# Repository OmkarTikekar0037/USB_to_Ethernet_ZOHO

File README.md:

# USB 3.1 Gen 1 to Gigabit Ethernet Adapter

A custom 4-layer PCB implementing a USB 3.1 Gen 1 to Gigabit Ethernet adapter based on the **Microchip LAN7801** USB-to-Ethernet controller and the **KSZ9031RNX** Gigabit Ethernet PHY.

The project focuses on producing a manufacturable hardware design by following industry-standard practices for high-speed PCB layout, power distribution, signal integrity, and Ethernet design.

---

## Project Objectives

- Design a production-quality USB 3.1 Gen 1 to Gigabit Ethernet adapter.
- Implement a complete RGMII-based Ethernet subsystem.
- Develop a reliable multi-rail power architecture.
- Follow high-speed PCB design guidelines for USB and Gigabit Ethernet.
- Produce fabrication-ready design files with zero ERC/DRC violations.

---

## Hardware Overview

| Component | Description |
|-----------|-------------|
| LAN7801 | USB 3.1 Gen 1 to Gigabit Ethernet Controller |
| KSZ9031RNX | Gigabit Ethernet PHY |
| 93LC56 | External configuration EEPROM |
| USB Type-C | USB Interface |
| RJ45 MagJack | Ethernet Connector with Integrated Magnetics |
| TLV76733 | 3.3V LDO |
| TPS7A0212 | 1.2V LDO |

---

## System Architecture

```
USB Type-C
      │
      ▼
+--------------+
|   LAN7801    |
+--------------+
      │
     RGMII
      │
      ▼
+--------------+
| KSZ9031RNX   |
+--------------+
      │
 Ethernet MDI
      │
      ▼
 RJ45 MagJack
```

---

## Repository Structure

```text
.
├── Hardware/
│   ├── Schematic/
│   ├── PCB/
│   ├── Libraries/
│   └── Manufacturing/
│
├── Docs/
│   ├── Project_History.md
│   ├── System_Architecture.md
│   ├── Power_Architecture.md
│   ├── Ethernet_Subsystem.md
│   ├── USB_Subsystem.md
│   ├── PCB_Design.md
│   └── Debugging.md
│
├── Datasheets/
│
├── Images/
│
└── README.md
```

---

## Current Project Status

| Stage | Status |
|--------|--------|
| Component Selection | Completed |
| Schematic Design | Completed |
| PCB Placement | Completed |
| PCB Routing | Completed |
| ERC | Passed |
| DRC | Passed |
| Manufacturing Outputs | In Progress |
| Hardware Validation | Pending |

---

## Design Highlights

- 4-layer PCB stack-up
- Controlled impedance routing
- USB differential pair routing
- Gigabit Ethernet differential routing
- Dedicated power planes
- Multi-stage power regulation
- External EEPROM configuration
- RGMII interface between MAC and PHY
- ESD and signal protection provisions

---

## Documentation

Detailed design discussions and engineering decisions are maintained separately under the **Docs** directory.

These documents describe:

- Architecture
- Design decisions
- Power subsystem
- PCB layout methodology
- Signal integrity considerations
- Manufacturing preparation
- Debugging history

The README intentionally provides only a high-level overview.

---

## Future Work

- PCB fabrication
- Assembly
- Hardware bring-up
- USB enumeration verification
- Ethernet link validation
- Throughput testing
- Compliance verification

---

## License

Project license to be added.

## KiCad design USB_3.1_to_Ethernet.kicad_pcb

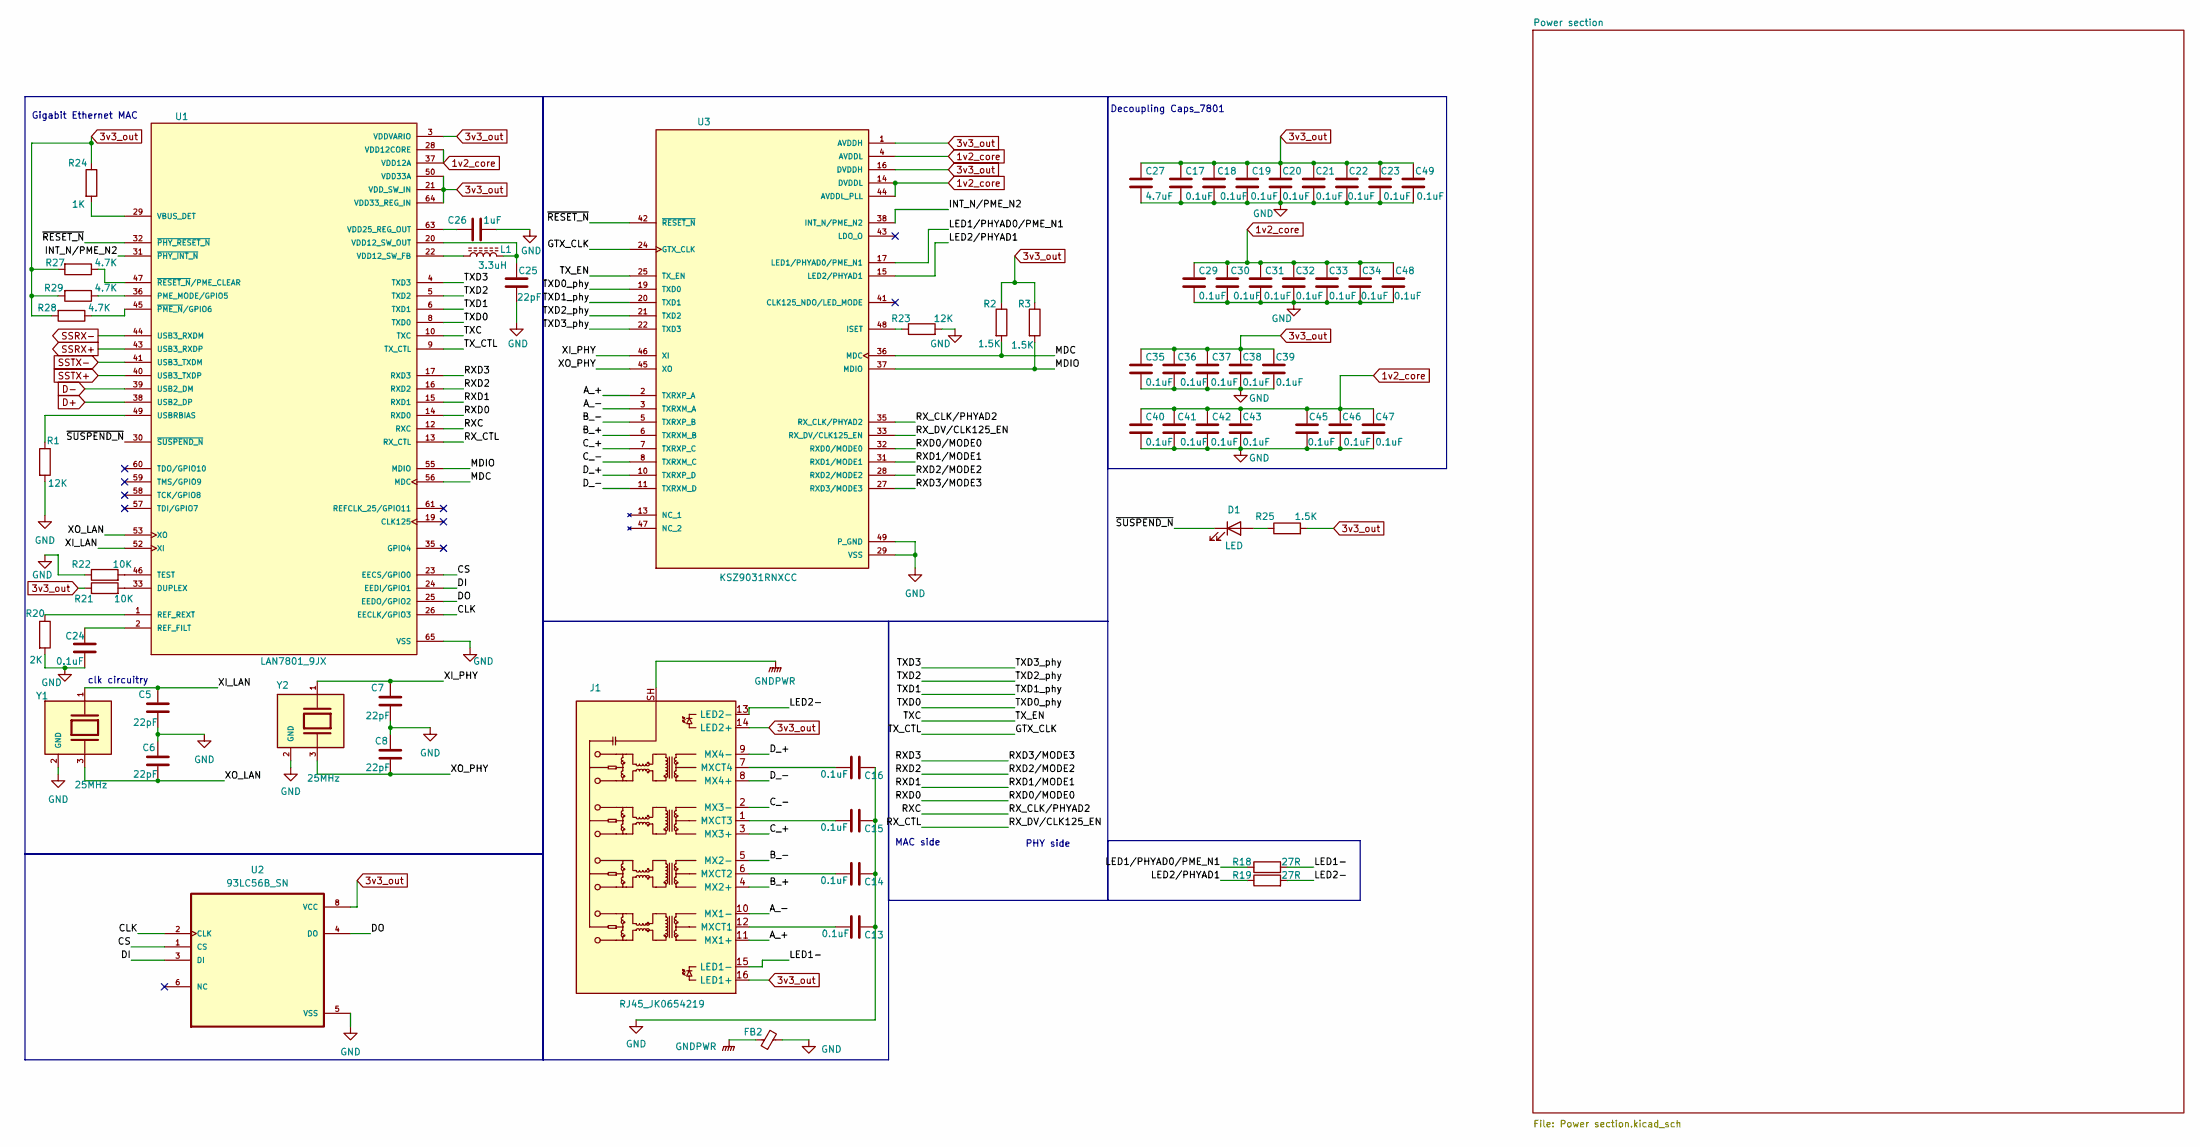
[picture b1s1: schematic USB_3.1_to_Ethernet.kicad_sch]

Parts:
C5, C6, C7, C8: 22pF; C_0402_1005Metric
C13, C14, C15, C16: 0.1uF; C_0402_1005Metric
C17, C18, C19, C20, C21, C22, C23, C24, C29, C30, C31, C32, C33, C34, C35, C36, C37, C38, C39, C40, C41, C42, C43, C45, C46, C47, C48, C49: 0.1uF; C_01005_0402Metric
C25: 22pF; C_01005_0402Metric
C26: 1uF; C_01005_0402Metric
C27: 4.7uF; C_01005_0402Metric
D1: LED; LED_01005_0402Metric
FB2: FerriteBead_Small; L_0402_1005Metric
J1: RJ45_JK0654219; RJ45_Pulse_JK0654219NL_Horizontal
L1: 3.3uH; L_0402_1005Metric
R1, R23: 12K; R_0402_1005Metric
R2, R3, R25: 1.5K; R_0402_1005Metric
R18, R19: 27R; R_0402_1005Metric
R20: 2K; R_0402_1005Metric
R21, R22: 10K; R_0402_1005Metric
R24: 1K; R_0402_1005Metric
R27, R28, R29: 4.7K; R_0402_1005Metric
U1: LAN7801_9JX; QFN50P900X900X100-65N_LAN7801_9JX; PARTREV DS00002123F
U2: 93LC56B_SN; 93LC56B_SOIC_8
U3: KSZ9031RNXCC; IC_KSZ9031RNXCC; PARTREV 07-09-24
Y1, Y2: 25MHz; Crystal_SMD_3225-4Pin_3.2x2.5mm; PARTREV August 01, 2022

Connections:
1v2_core: C29.1, C30.1, C31.1, C32.1, C33.1, C34.1, C40.1, C41.1, C42.1, C43.1, C45.1, C46.1, C47.1, C48.1, U1.28 (VDD12CORE), U1.37 (VDD12A), U1.42 (VDD12A), U1.54 (VDD12CORE), U1.62 (VDD12A), U3.4 (AVDDL), U3.9 (AVDDL), U3.14 (DVDDL), U3.18 (DVDDL), U3.23 (DVDDL), U3.26 (DVDDL), U3.30 (DVDDL), U3.39 (DVDDL), U3.44 (AVDDL_PLL); also elsewhere on the board
3v3_out: C17.1, C18.1, C19.1, C20.1, C21.1, C22.1, C23.1, C27.1, C35.1, C36.1, C37.1, C38.1, C39.1, C49.1, J1.14 (LED2+), J1.16 (LED1+), R2.1, R3.1, R21.1, R24.1, R25.2, R27.2, R28.2, R29.2, U1.3 (VDDVARIO), U1.7 (VDDVARIO), U1.11 (VDDVARIO), U1.18 (VDDVARIO), U1.21 (VDD_SW_IN), U1.27 (VDDVARIO), U1.48 (VDDVARIO), U1.50 (VDD33A), U1.51 (VDDVARIO), U1.64 (VDD33_REG_IN), U2.8 (VCC), U3.1 (AVDDH), U3.12 (AVDDH), U3.16 (DVDDH), U3.34 (DVDDH), U3.40 (DVDDH); also elsewhere on the board
/A_+: J1.11 (MX1+), U3.2 (TXRXP_A)
/A_-: J1.10 (MX1-), U3.3 (TXRXM_A)
/B_+: J1.4 (MX2+), U3.6 (TXRXM_B)
/B_-: J1.5 (MX2-), U3.5 (TXRXP_B)
/CLK: U1.26 (EECLK/GPIO3), U2.2 (CLK)
/CS: U1.23 (EECS/GPIO0), U2.1 (CS)
/C_+: J1.3 (MX3+), U3.7 (TXRXP_C)
/C_-: J1.2 (MX3-), U3.8 (TXRXM_C)
/DI: U1.24 (EEDI/GPIO1), U2.3 (DI)
/DO: U1.25 (EEDO/GPIO2), U2.4 (DO)
/D_+: J1.9 (MX4-), U3.10 (TXRXP_D)
/D_-: J1.8 (MX4+), U3.11 (TXRXM_D)
/GTX_CLK: U1.9 (TX_CTL), U3.24 (GTX_CLK)
/INT_N/PME_N2: U1.31 (~PHY_INT_N), U3.38 (INT_N/PME_N2)
/LED1-: J1.15 (LED1-), R18.2
/LED1/PHYAD0/PME_N1: R18.1, U3.17 (LED1/PHYAD0/PME_N1)
/LED2-: J1.13 (LED2-), R19.2
/LED2/PHYAD1: R19.1, U3.15 (LED2/PHYAD1)
/MDC: R2.2, U1.56 (MDC), U3.36 (MDC)
/MDIO: R3.2, U1.55 (MDIO), U3.37 (MDIO)
/RXD0: U1.14 (RXD0), U3.32 (RXD0/MODE0)
/RXD1: U1.15 (RXD1), U3.31 (RXD1/MODE1)
/RXD2: U1.16 (RXD2), U3.28 (RXD2/MODE2)
/RXD3: U1.17 (RXD3), U3.27 (RXD3/MODE3)
/RX_CTL: U1.13 (RX_CTL), U3.33 (RX_DV/CLK125_EN)
/TXC: U1.10 (TXC), U3.25 (TX_EN)
/TXD0: U1.8 (TXD0), U3.19 (TXD0)
/TXD1: U1.6 (TXD1), U3.20 (TXD1)
/TXD2: U1.5 (TXD2), U3.21 (TXD2)
/TXD3: U1.4 (TXD3), U3.22 (TXD3)
/XI_LAN: C5.1, U1.52 (XI), Y1.1
/XI_PHY: C7.1, U3.46 (XI), Y2.1
/XO_LAN: C6.2, U1.53 (XO), Y1.3
/XO_PHY: C8.2, U3.45 (XO), Y2.3
/~RESET_N: U1.32 (~PHY_RESET_N), U3.42 (~RESET_N)
/~SUSPEND_N: D1.1 (K), U1.30 (~SUSPEND_N)
D+: U1.38 (USB2_DP); also elsewhere on the board
D-: U1.39 (USB2_DM); also elsewhere on the board
GND: C5.2, C6.1, C7.2, C8.1, C13.1, C14.1, C15.1, C16.1, C17.2, C18.2, C19.2, C20.2, C21.2, C22.2, C23.2, C24.2, C25.2, C26.2, C27.2, C29.2, C30.2, C31.2, C32.2, C33.2, C34.2, C35.2, C36.2, C37.2, C38.2, C39.2, C40.2, C41.2, C42.2, C43.2, C45.2, C46.2, C47.2, C48.2, C49.2, FB2.2, R1.2, R20.2, R22.1, R23.2, U1.65 (VSS), U2.5 (VSS), U3.29 (VSS), U3.49 (P_GND), U3.49_1 (P_GND), U3.49_2 (P_GND), U3.49_3 (P_GND), U3.49_4 (P_GND), U3.49_5 (P_GND), U3.49_6 (P_GND), U3.49_7 (P_GND), U3.49_8 (P_GND), U3.49_9 (P_GND), U3.49_10 (P_GND), U3.49_11 (P_GND), U3.49_12 (P_GND), U3.49_13 (P_GND), U3.49_14 (P_GND), U3.49_15 (P_GND), U3.49_16 (P_GND), U3.49_17 (P_GND), U3.49_18 (P_GND), U3.49_19 (P_GND), U3.49_20 (P_GND), U3.49_21 (P_GND), U3.49_22 (P_GND), U3.49_23 (P_GND), U3.49_24 (P_GND), U3.49_25 (P_GND), Y1.2 (GND), Y1.4 (GND), Y2.2 (GND), Y2.4 (GND); also elsewhere on the board
GNDPWR: FB2.1, J1.SH
unnamed: D1.2 (A), R25.1
unnamed: C13.2, J1.12 (MXCT1)
unnamed: C14.2, J1.6 (MXCT2)
unnamed: C15.2, J1.1 (MXCT3)
unnamed: C16.2, J1.7 (MXCT4)
unnamed: R21.2, U1.33 (DUPLEX)
unnamed: R29.1, U1.36 (PME_MODE/GPIO5)
unnamed: C24.1, U1.2 (REF_FILT)
unnamed: R20.1, U1.1 (REF_REXT)
unnamed: R22.2, U1.46 (TEST)
unnamed: R1.1, U1.49 (USBRBIAS)
unnamed: R24.2, U1.29 (VBUS_DET)
unnamed: L1.1, U1.22 (VDD12_SW_FB)
unnamed: C25.1, L1.2, U1.20 (VDD12_SW_OUT)
unnamed: C26.1, U1.63 (VDD25_REG_OUT)
unnamed: R28.1, U1.45 (~PME_N/GPIO6)
unnamed: R27.1, U1.47 (~RESET_N/PME_CLEAR)
unnamed: R23.1, U3.48 (ISET)
SSRX+: U1.43 (USB3_RXDP); also elsewhere on the board
SSRX-: U1.44 (USB3_RXDM); also elsewhere on the board
SSTX+: U1.40 (USB3_TXDP); also elsewhere on the board
SSTX-: U1.41 (USB3_TXDM); also elsewhere on the board

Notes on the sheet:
Decoupling Caps_7801
clk circuitry
Gigabit Ethernet MAC
PHY side
MAC side

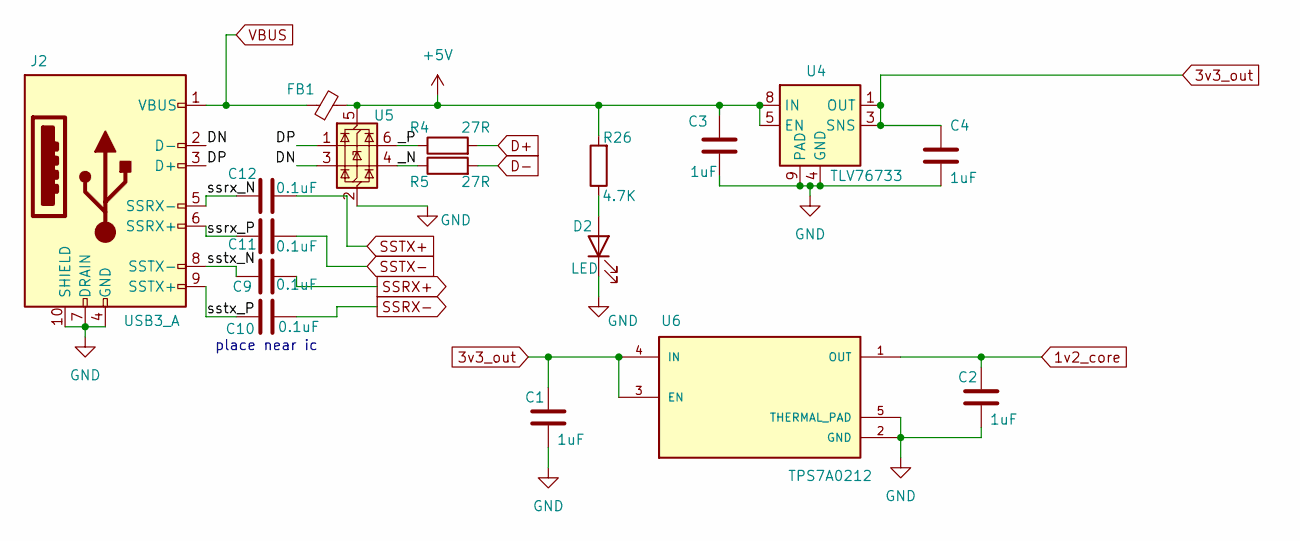
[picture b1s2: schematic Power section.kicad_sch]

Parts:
C1, C2, C3, C4: 1uF; C_0402_1005Metric
C9, C10, C11, C12: 0.1uF; C_0402_1005Metric
D2: LED; LED_01005_0402Metric
FB1: FerriteBead_Small; L_0402_1005Metric
J2: USB3_A; USB3_A_Plug_Wuerth_692112030100_Horizontal
R4, R5: 27R; R_0402_1005Metric
R26: 4.7K; R_0402_1005Metric
U4: TLV76733; VSON-8-1EP_3x3mm_P0.65mm_EP1.65x2.4mm_ThermalVias
U5: USBLC6-2P6; SOT-666
U6: TPS7A0212; Tps_7a0212; PARTREV C

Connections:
1v2_core: C2.1, U6.1 (OUT); also elsewhere on the board
3v3_out: C1.1, C4.1, U4.1 (OUT), U4.3 (SNS), U6.3 (EN), U6.4 (IN); also elsewhere on the board
+5V: C3.1, FB1.2, R26.2, U4.5 (EN), U4.8 (IN), U5.5 (VBUS)
/Power section/DN: J2.2 (D-), U5.3 (I/O2)
/Power section/DP: J2.3 (D+), U5.1 (I/O1)
/Power section/_N: R5.1, U5.4 (I/O2)
/Power section/_P: R4.1, U5.6 (I/O1)
/Power section/ssrx_N: C12.1, J2.5 (SSRX-)
/Power section/ssrx_P: C11.1, J2.6 (SSRX+)
/Power section/sstx_N: C9.1, J2.8 (SSTX-)
/Power section/sstx_P: C10.1, J2.9 (SSTX+)
D+: R4.2; also elsewhere on the board
D-: R5.2; also elsewhere on the board
GND: C1.2, C2.2, C3.2, C4.2, D2.1 (K), J2.4 (GND), J2.7 (DRAIN), J2.10 (SHIELD), U4.4 (GND), U4.6 (GND), U4.9 (PAD), U5.2 (GND), U6.2 (GND), U6.5 (THERMAL_PAD); also elsewhere on the board
unnamed: D2.2 (A), R26.1
SSRX+: C9.2; also elsewhere on the board
SSRX-: C10.2; also elsewhere on the board
SSTX+: C12.2; also elsewhere on the board
SSTX-: C11.2; also elsewhere on the board
VBUS: FB1.1, J2.1 (VBUS)

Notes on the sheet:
place near ic

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
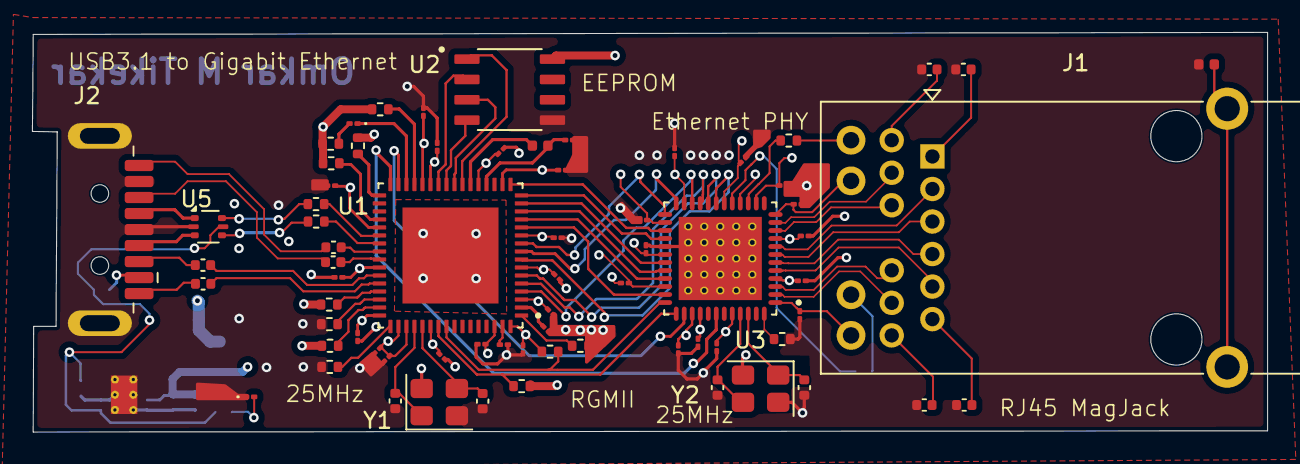
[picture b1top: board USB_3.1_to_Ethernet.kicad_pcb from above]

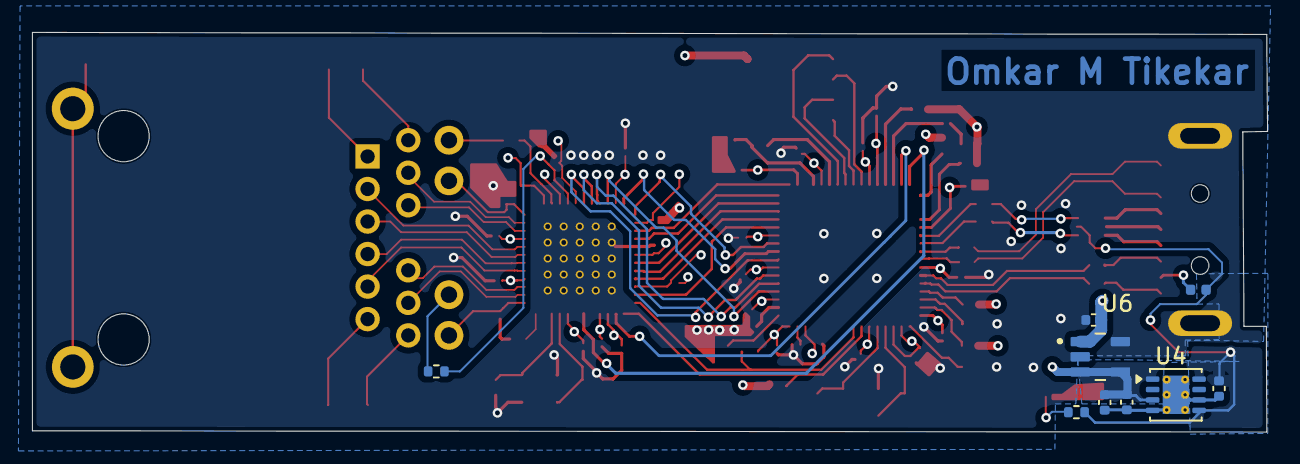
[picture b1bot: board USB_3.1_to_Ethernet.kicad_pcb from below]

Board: 4 copper layers, 77.2 x 25.0 mm, 79 parts (9 on the bottom side), 76 nets.

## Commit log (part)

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2026-04-10 usb connector added
2026-04-10 tvs-FB-ldo-symbol-footprint
2026-04-10 power section added and power connections done
2026-04-10 power section added and power connections made
2026-04-10 power section added and power conections made
2026-04-10 usb connections done without 27 ohm, SMI connections done, EEPROM connections done.
2026-04-10 nothing changed : linked to remote repo
2026-04-10 cleaned up the messy file system
2026-04-10 RGMII connections made, Clk circuitry made, 27 ohm resistors added
2026-04-13 Added 27R resistors to RGMII interface, added 0.1uF AC coupling caps on sstx/rx, Magjack connections done
2026-04-13 nothing changed, just cleaned up the timeline
2026-05-09 no major changes, APll tied to 3v3
2026-05-09 1. Decoupling capacitors for Lan7801 ic added 2. 3.3v Input given to TPS7A0212 instead of 5v 3. Ref+Rfilt resistor capacitor added 4. Iset resistor 12K added 5. Test Pull-down and Duplex Pull-up 10K 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
2026-05-23 1. Layout placement started. placed Lan7801, PHY, EEPROM and regulators 2.changed D+ D- lines of USB-TVS diode reveresed for clean routing
2026-05-24 merged with main branch, no major change in pcb or schematics
2026-05-26 1. net class assigned to all the nets 2.Slight placement changes
2026-05-27 1. Major routing done- usb3.1,usb2, >> 2. buck converter and voltage regulators placement and routing done >> 3. Decoupling caps added
2026-05-27 1. usb routing done 2.clock routing done 3. decoupling capacitors(3.3v) routing for lan7801 ic done
2026-05-29 1. RGMII routing done - LAN7801 RXD 2.Routing for RGMII - TXD on top layer done, bottom layer remaining 3. source termination resistors 27 ohm removed for RGMII
2026-05-30 rgmii routing completed
2026-05-30 1.complete routing done 2.Ethernet MDI differential routing done 3.power and gnd plane on L2 and L3 completed 4.
2026-05-30 microadjustments in via connections of gnd
2026-05-30 cleaned the DRC errors and step files of ICs included
2026-06-07 step file for usb A plug added. Modified edge cuts layer by adding a slot for usb connector'
2026-06-07 adjusted via positions near the PHY ic
2026-06-07 tvs diode routing complete and improved usb2 routing
2026-06-12 step files for all the component added
